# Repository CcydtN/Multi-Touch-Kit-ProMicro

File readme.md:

# Multi-Touch-Kit-ProMicro

As the title suggests, this project is trying to reproduce the result of [Multi-Touch kit](https://hci.cs.uni-saarland.de/projects/multi-touch-kit/) with a ProMicro board.

---
## Demo
https://user-images.githubusercontent.com/51289140/219960157-e1035877-1ed2-4f21-ac63-bcd13f59a0d3.mp4
> The demo is using the source code from "experiment" branch (See Note.2)

> The two axis in the demo is a mess, but I am not planning to fixed it in short term.
---
## Preparation
In this repo:
- A python script to create the grid
- A KiCad project for the pcb design
- The source code for the ProMicro
- Clone of [Multi-Touch Kit Processing code](https://github.com/HCI-Lab-Saarland/MultiTouchKitUI)

Not in the repo:
- [PlatformIO](https://platformio.org/)
- [Processing](https://processing.org/)

---
## Procedure
Most steps is following the Multi-Touch Kit Project
1. Create a schemetic
2. Print out the PCB and prepare the components
3. Connect all pins and wires
4. Upload the code through PlatformIO
5. Use Processing to observe the result

---
## Note
1. Readings from R1 seem having a lot of noise and effecting the result, so it is disabled.
2. "Experiment" branch seem to have a better performance. I am trying to figure out the reason, feel free to comment in the [issue](https://github.com/CcydtN/Multi-Touch-Kit-ProMicro/issues/2).

---
Reference:
- [Multi-Touch Kit](https://hci.cs.uni-saarland.de/projects/multi-touch-kit/)
    - The Starting point of this project
- [Sensor Design Guidelines](http://ww1.microchip.com/downloads/en/DeviceDoc/FAQs%20-%20Sensor%20Design%20Guidelines.pdf)
    - More detail about pcb design can be found here.
    - The python script for generating grid is base on this document.
- [Pro Micro & Fio V3 Hookup Guide](https://learn.sparkfun.com/tutorials/pro-micro--fio-v3-hookup-guide/hardware-overview-pro-micro)
    - Pin layout about ProMicro

---
## Future Plan
- [ ] Learn about USB-HID
  - https://www.usb.org/hid
  - https://docs.kernel.org/hid/index.html
  - https://learn.microsoft.com/en-us/windows-hardware/design/component-guidelines/touchpad-sample-report-descriptors
  - https://github.com/smulikHakipod/USB-Emulation/tree/master

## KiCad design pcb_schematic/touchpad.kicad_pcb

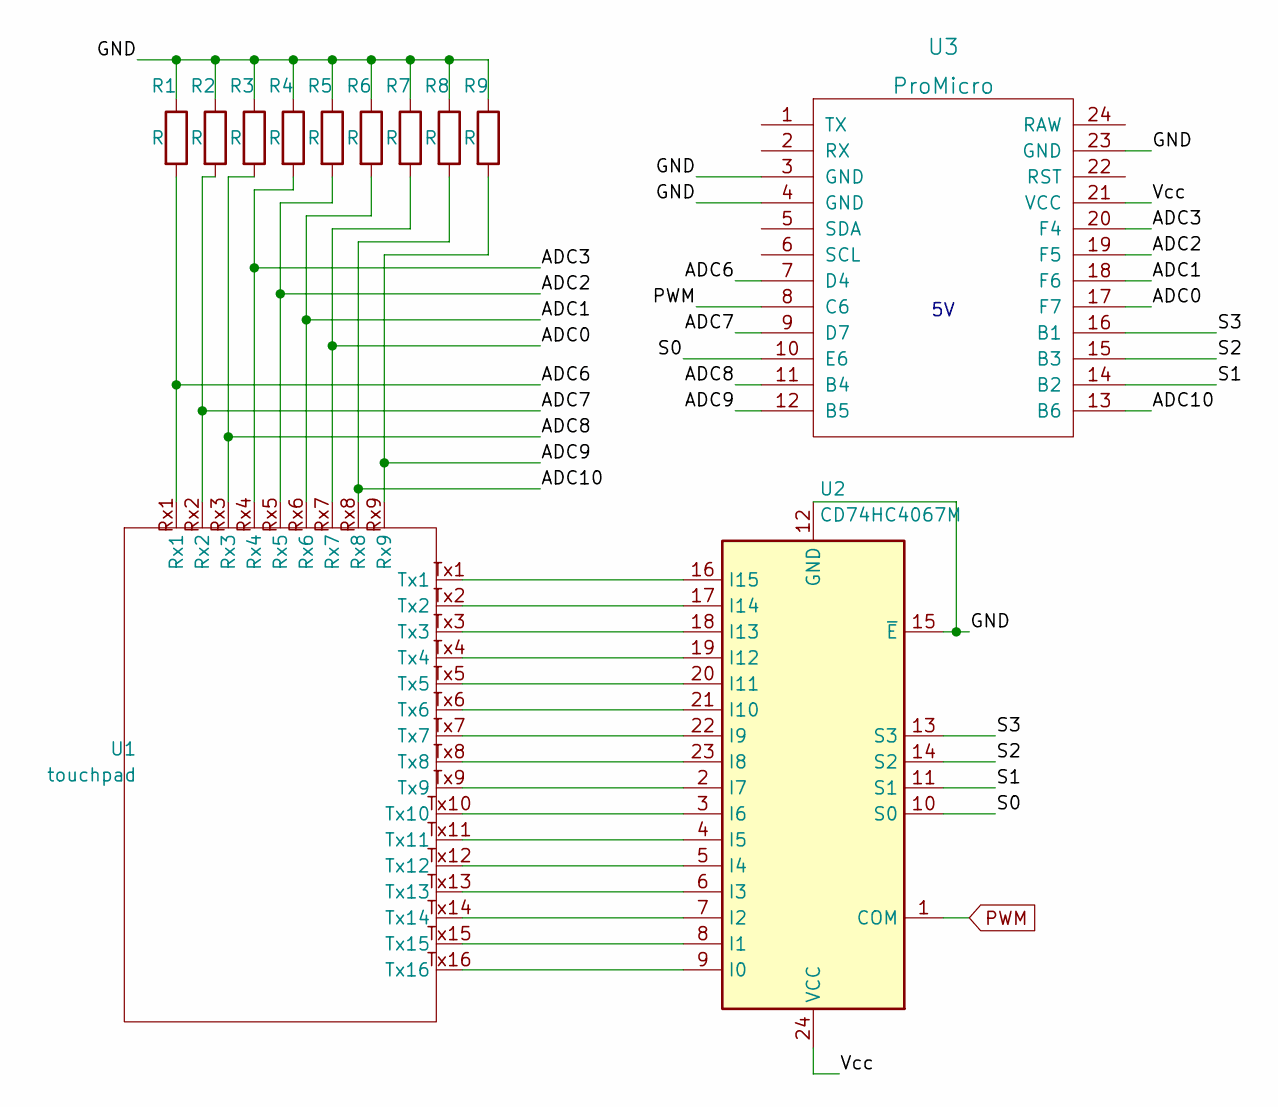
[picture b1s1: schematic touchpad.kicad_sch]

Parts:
R1, R2, R3, R4, R5, R6, R7, R8, R9: R; R_0805_2012Metric
U1: touchpad
U2: CD74HC4067M; SOIC-24W_7.5x15.4mm_P1.27mm
U3: ProMicro

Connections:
/ADC0: R7.2, U1.Rx7, U3.17 (F7)
/ADC1: R6.2, U1.Rx6, U3.18 (F6)
/ADC2: R5.2, U1.Rx5, U3.19 (F5)
/ADC3: R4.2, U1.Rx4, U3.20 (F4)
/ADC6: R1.2, U1.Rx1, U3.7 (D4)
/ADC7: R2.2, U1.Rx2, U3.9 (D7)
/ADC8: R3.2, U1.Rx3, U3.11 (B4)
/ADC9: R9.2, U1.Rx9, U3.12 (B5)
/ADC10: R8.2, U1.Rx8, U3.13 (B6)
/GND: R1.1, R2.1, R3.1, R4.1, R5.1, R6.1, R7.1, R8.1, R9.1, U2.12 (GND), U2.15 (~E), U3.3 (GND), U3.4 (GND), U3.23 (GND)
/S0: U2.10 (S0), U3.10 (E6)
/S1: U2.11 (S1), U3.14 (B2)
/S2: U2.14 (S2), U3.15 (B3)
/S3: U2.13 (S3), U3.16 (B1)
/Vcc: U2.24 (VCC), U3.21 (VCC)
unnamed: U1.Tx1, U2.16 (I15)
unnamed: U1.Tx2, U2.17 (I14)
unnamed: U1.Tx3, U2.18 (I13)
unnamed: U1.Tx4, U2.19 (I12)
unnamed: U1.Tx5, U2.20 (I11)
unnamed: U1.Tx6, U2.21 (I10)
unnamed: U1.Tx7, U2.22 (I9)
unnamed: U1.Tx8, U2.23 (I8)
unnamed: U1.Tx9, U2.2 (I7)
unnamed: U1.Tx10, U2.3 (I6)
unnamed: U1.Tx11, U2.4 (I5)
unnamed: U1.Tx12, U2.5 (I4)
unnamed: U1.Tx13, U2.6 (I3)
unnamed: U1.Tx14, U2.7 (I2)
unnamed: U1.Tx15, U2.8 (I1)
unnamed: U1.Tx16, U2.9 (I0)
PWM: U2.1 (COM), U3.8 (C6)

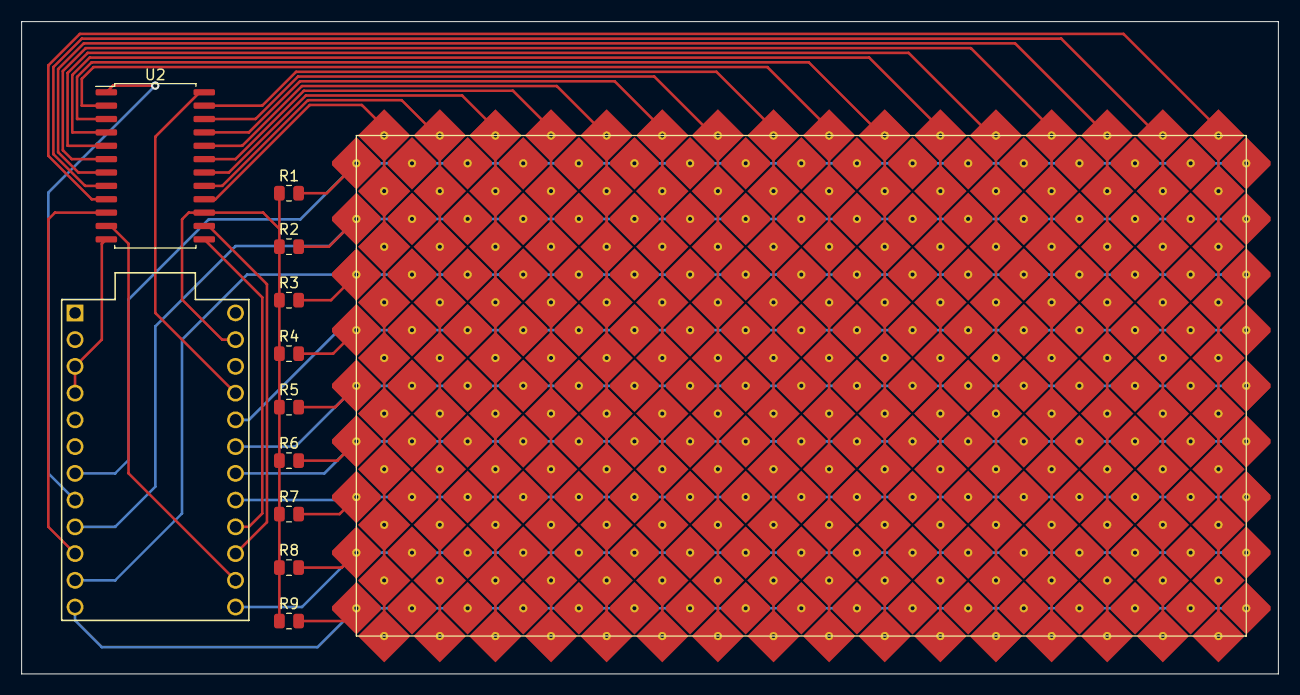
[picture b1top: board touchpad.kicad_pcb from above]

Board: 2 copper layers, 119.4 x 62.0 mm, 12 parts (0 on the bottom side), 32 nets.

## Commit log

2023-02-18 First Commit!!!
2023-02-19 Fix PCB tag naming
2023-02-19 Add readme.md
2023-02-19 Using another clock
2023-02-19 Update PCB
2023-02-19 Add the modified version of Processing Code, and some minor fix
2023-02-19 Add video to readme.md
2024-07-06 Update future plan and reference
2024-10-06 Create LICENSE
2024-10-06 Update LICENSE
